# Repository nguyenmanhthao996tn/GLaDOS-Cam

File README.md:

# GLaDOS-Cam

> Edge AI IoT board for vision-based applications

---

## Overview

GLaDOS-Cam is a custom PCB built around the **STM32U575VIT6** (Cortex-M33, 160 MHz) targeting battery-powered, field-deployed TinyML inference. No NPU. No cloud. Runs INT8 inference locally at 1–2 fps which is all that's needed.

---

## Hardware

| # | Component | Manufacturer | Part No. | JLCPCB |
|---|---|---|---|---|
| 1 | MCU | STMicroelectronics | STM32U575**VIT6** | C5270999 |
| 2 | PSRAM | ISSI | IS66WVH8M8BLL-100B1LI | C1349096 |
| 3 | LDO (3.3 V aux) | STMicroelectronics | STLQ020C33R | C2970558 |
| 4 | Camera connector | Hirose | FH12-24S-0.5SH(55) | C202112 |
| 5 | Camera AVDD LDO (2.8 V) | YONGYUTAI | XC6206-2.8V | C2892669 |
| 6 | Camera DVDD LDO (1.2 V) | YONGYUTAI | XC6206-1.2V | C49446790 |
| 7 | Crystal 16 MHz | YXC | X322516MLB4SI | C13738 |
| 8 | Crystal 32.768 kHz | Seiko Epson | Q13FC13500004 | C32346 |
| 9 | Reset button | XKB Connection | TS-1187A-B-A-B | C318884 |
| 10 | MicroSD slot | SHOU HAN | TF-CARD H1.8 | C7529389 |

## Toolchain

| Tool | Purpose |
|---|---|
| KiCad 9 | Schematic + PCB layout |

---

## Repo Structure

```
GLaDOS-Cam/
├── docs/                          # Datasheets, BOM references
│   ├── Component_List.xlsx
│   ├── ESP32_CAM_V1.6.pdf
│   └── NUCLEO-U575ZI-Q/
└── pcb/
    └── GLaDOS-Cam/
        ├── GLaDOS-Cam.kicad_pro   # Project root
        ├── GLaDOS-Cam.kicad_sch   # Top-level schematic
        ├── GLaDOS-Cam.kicad_pcb   # PCB layout
        ├── cam_conn.kicad_sch     # Camera connector sub-sheet
        ├── io_headers.kicad_sch
        ├── mcu.kicad_sch
        ├── microsd.kicad_sch
        ├── power.kicad_sch
        ├── psram.kicad_sch
        └── glados-cam-lib/        # Project-local KiCad library
            ├── glados-cam-lib.pretty/   # Footprints
            │   └── 3d_models/           # STEP files
            └── symbols/
```

---

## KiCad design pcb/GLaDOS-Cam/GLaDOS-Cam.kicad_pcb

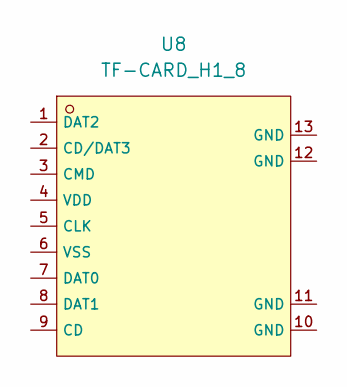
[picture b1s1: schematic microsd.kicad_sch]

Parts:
U8: TF-CARD_H1_8; TF-SMD_TF-CARD-H1.8; LCSC C7529389

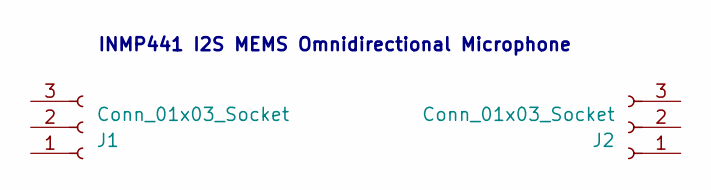
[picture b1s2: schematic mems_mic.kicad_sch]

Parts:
J1, J2: Conn_01x03_Socket; PinSocket_1x03_P2.54mm_Vertical

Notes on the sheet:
INMP441 I2S MEMS Omnidirectional Microphone

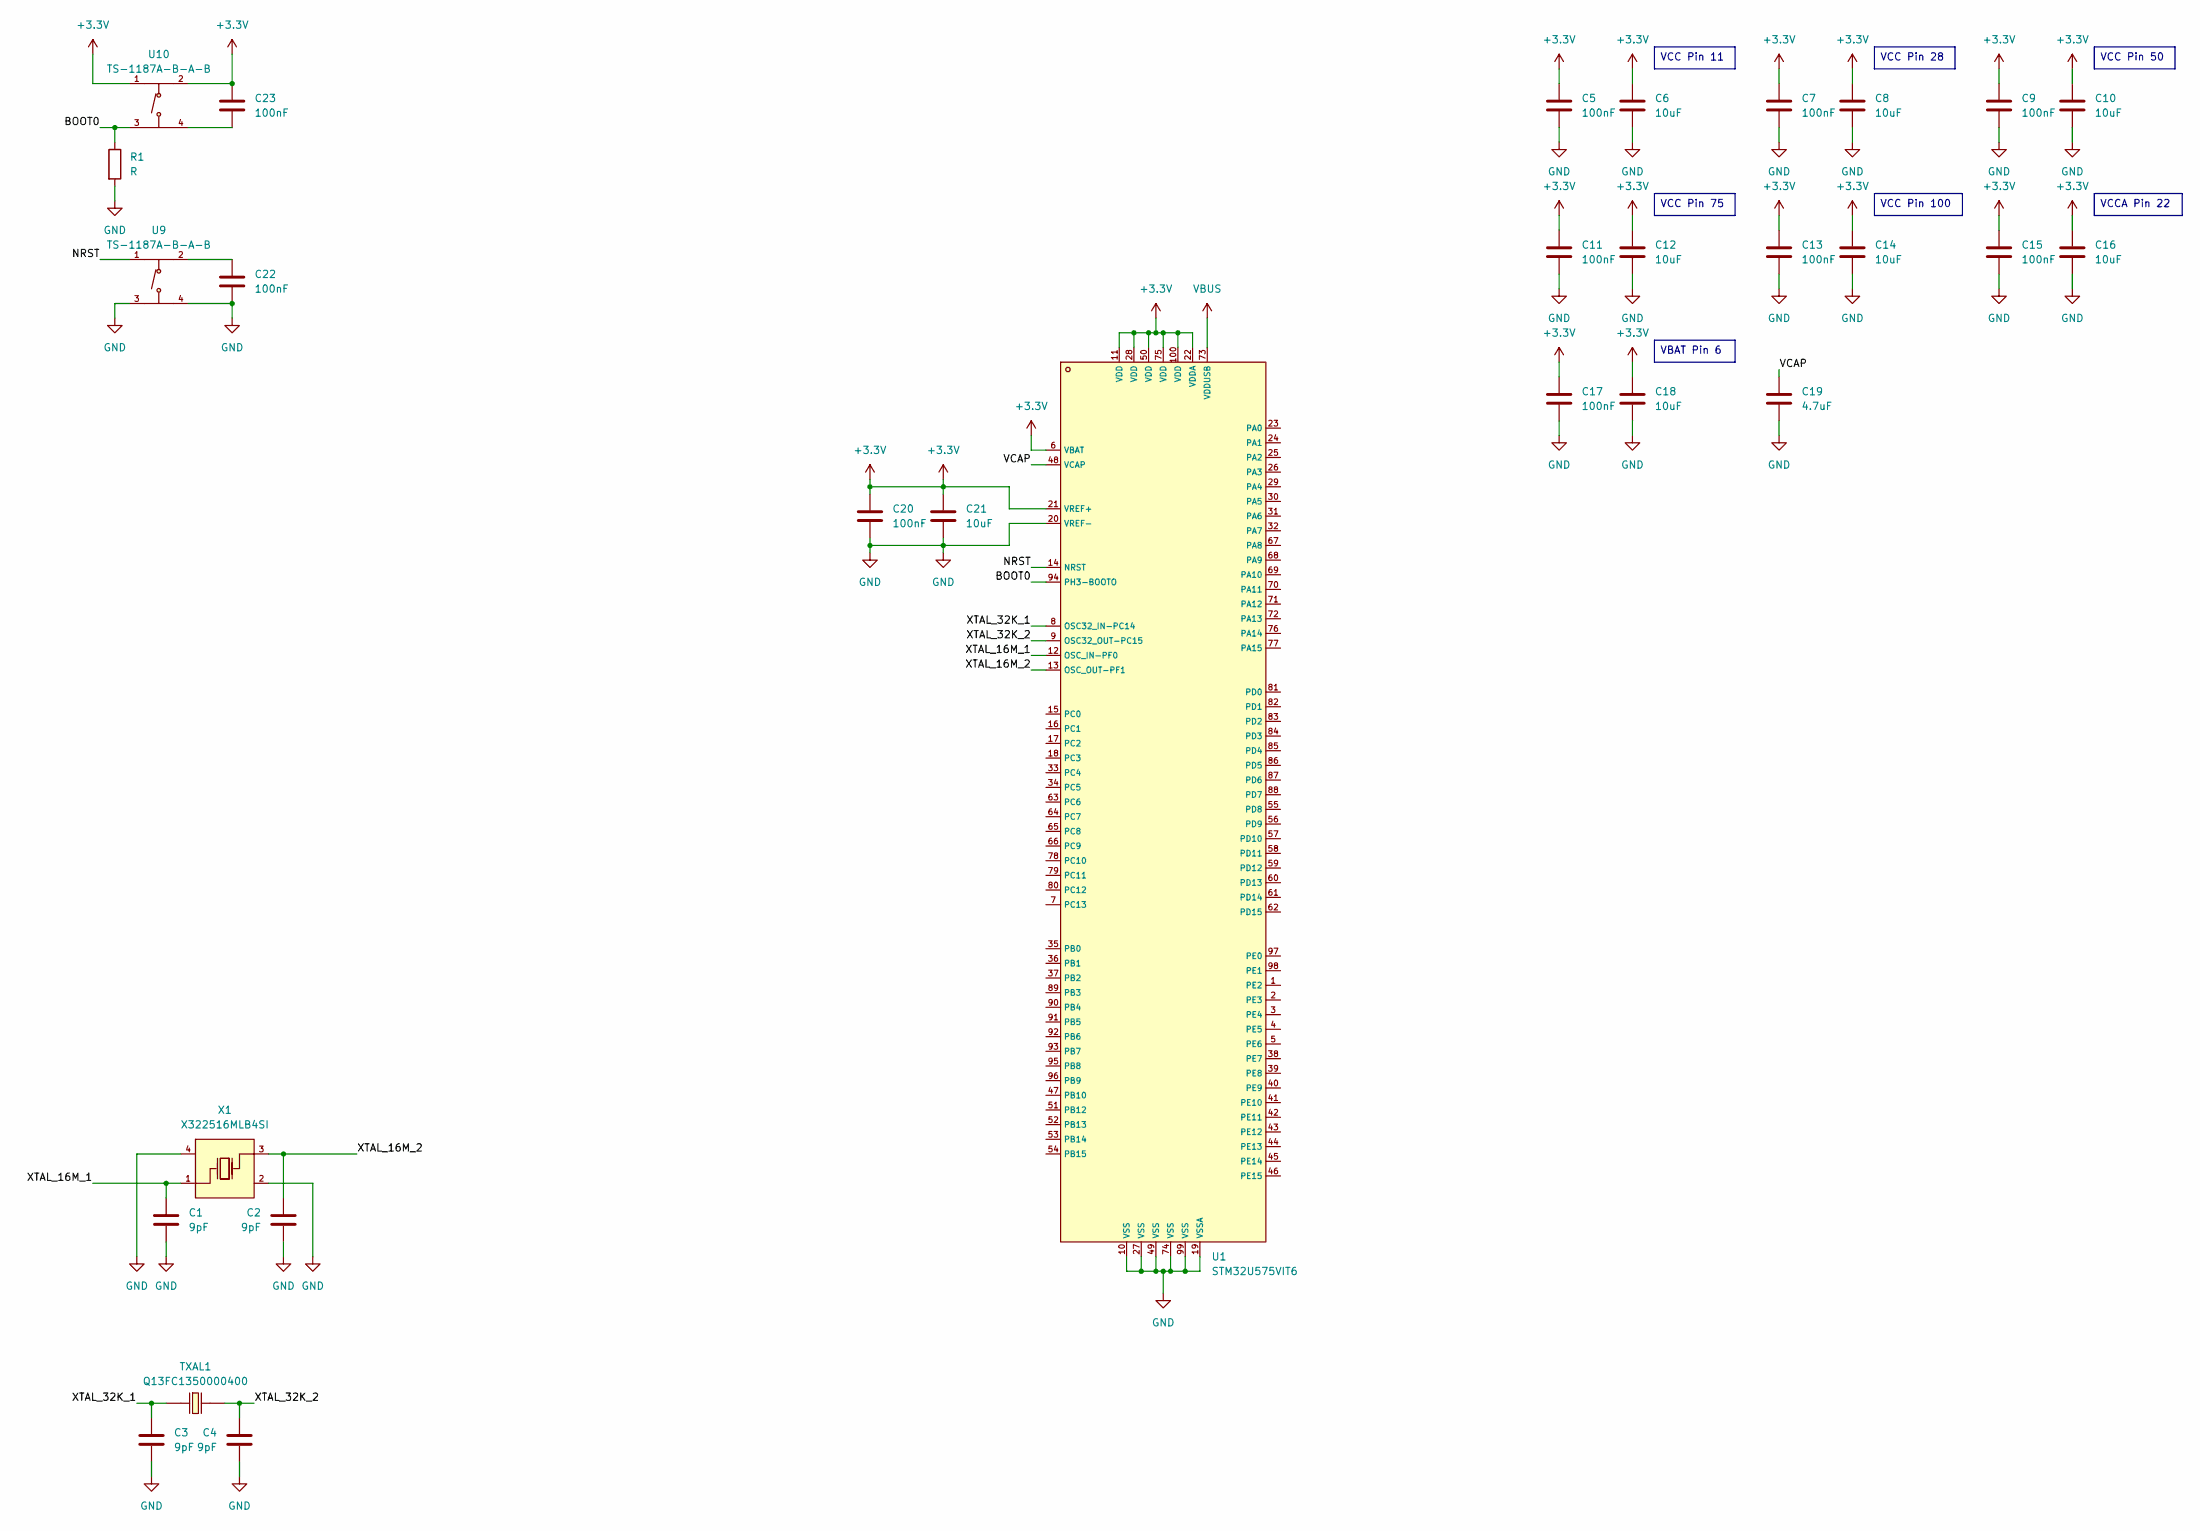
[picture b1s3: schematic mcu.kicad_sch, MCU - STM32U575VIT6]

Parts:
C1, C2, C3, C4: 9pF; C_0603_1608Metric_Pad1.08x0.95mm_HandSolder
C5, C7, C9, C11, C13, C15, C17, C20, C22, C23: 100nF; C_0603_1608Metric_Pad1.08x0.95mm_HandSolder
C6, C8, C10, C12, C14, C16, C18, C21: 10uF; C_0603_1608Metric_Pad1.08x0.95mm_HandSolder
C19: 4.7uF; C_0603_1608Metric_Pad1.08x0.95mm_HandSolder
R1: R; R_0603_1608Metric_Pad0.98x0.95mm_HandSolder
TXAL1: Q13FC1350000400; FC-135R_L3.2-W1.5; LCSC C32346
U1: STM32U575VIT6; LQFP-100_L14.0-W14.0-P0.50-LS16.0-BL; LCSC C5270999
U9, U10: TS-1187A-B-A-B; SW-SMD_4P-L5.1-W5.1-P3.70-LS6.5-TL_H1.5; LCSC C318884
X1: X322516MLB4SI; CRYSTAL-SMD_4P-L3.2-W2.5-BL; LCSC C13738

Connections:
+3.3V: C5.1, C6.1, C7.1, C8.1, C9.1, C10.1, C11.1, C12.1, C13.1, C14.1, C15.1, C16.1, C17.1, C18.1, C20.1, C21.1, C23.1, U1.6 (VBAT), U1.11 (VDD), U1.21 (VREF+), U1.22 (VDDA), U1.28 (VDD), U1.50 (VDD), U1.75 (VDD), U1.100 (VDD), U10.1 (A), U10.2 (B)
/MCU/BOOT0: R1.1, U1.94 (PH3-BOOTO), U10.3 (C)
/MCU/NRST: U1.14 (NRST), U9.1 (A)
/MCU/VCAP: C19.1, U1.48 (VCAP)
/MCU/XTAL_16M_1: C1.1, U1.12 (OSC_IN-PF0), X1.1 (OSC1)
/MCU/XTAL_16M_2: C2.1, U1.13 (OSC_OUT-PF1), X1.3 (OSC2)
/MCU/XTAL_32K_1: C3.1, TXAL1.1, U1.8 (OSC32_IN-PC14)
/MCU/XTAL_32K_2: C4.1, TXAL1.2, U1.9 (OSC32_OUT-PC15)
GND: C1.2, C2.2, C3.2, C4.2, C5.2, C6.2, C7.2, C8.2, C9.2, C10.2, C11.2, C12.2, C13.2, C14.2, C15.2, C16.2, C17.2, C18.2, C19.2, C20.2, C21.2, C22.2, R1.2, U1.10 (VSS), U1.19 (VSSA), U1.20 (VREF-), U1.27 (VSS), U1.49 (VSS), U1.74 (VSS), U1.99 (VSS), U9.3 (C), U9.4 (D), X1.2 (GND), X1.4 (GND)
unnamed: C22.1, U9.2 (B)
unnamed: C23.2, U10.4 (D)
VBUS: U1.73 (VDDUSB)

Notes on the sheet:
VCC Pin 11
VCC Pin 50
VCCA Pin 22
VCC Pin 100
VCC Pin 75
VCC Pin 28
VBAT Pin 6

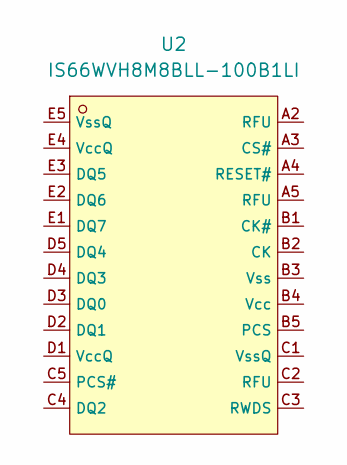
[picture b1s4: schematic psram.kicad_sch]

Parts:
U2: IS66WVH8M8BLL-100B1LI; TFBGA-24_L8.0-W6.0-P1.00-TL_ISSI_ISS66WVH16M8; LCSC C1349096

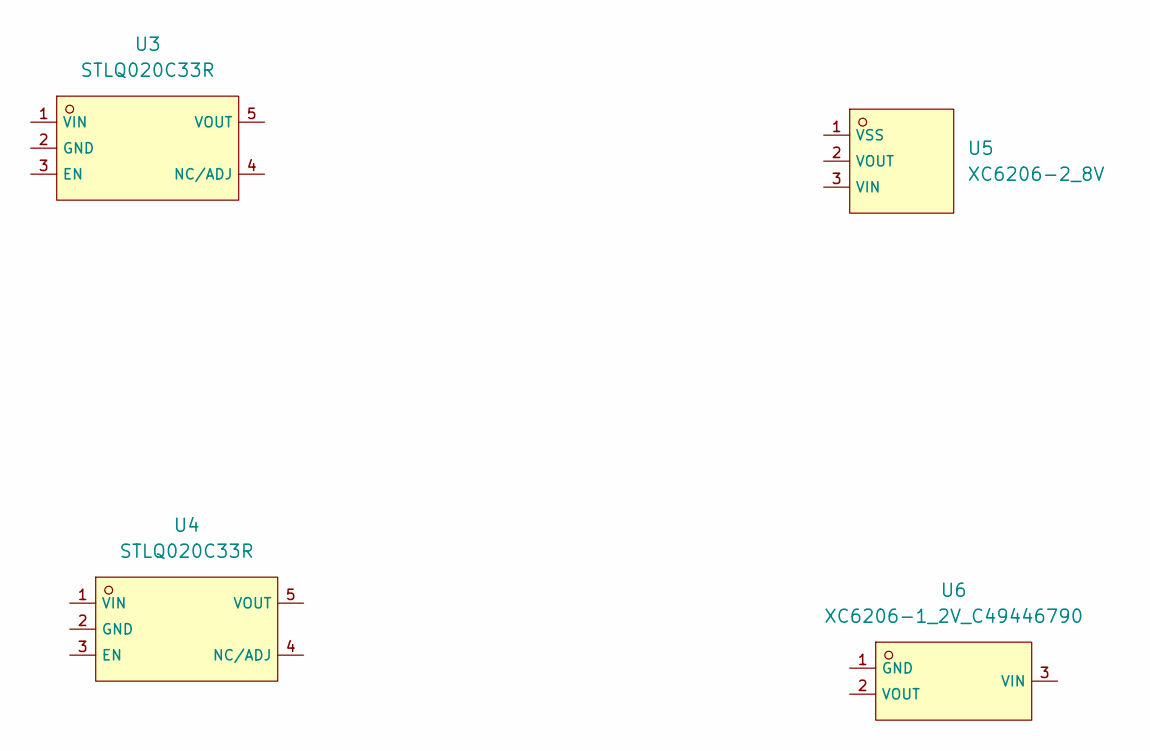
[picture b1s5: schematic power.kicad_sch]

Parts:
U3, U4: STLQ020C33R; TSSOP-5_L2.0-W1.3-P0.65-LS2.1-BL; LCSC C2970558
U5: XC6206-2_8V; SOT-23-3_L2.9-W1.6-P1.90-LS2.8-BR; LCSC C2892669
U6: XC6206-1_2V_C49446790; SOT-23-3_L3.0-W1.6-P1.90-LS2.8-BR; LCSC C49446790

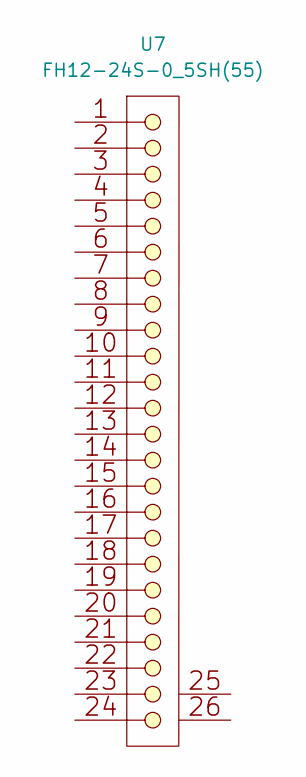
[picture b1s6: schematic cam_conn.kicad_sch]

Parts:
U7: FH12-24S-0_5SH(55); FPC-SMD_FH12-24S-0.5SH-55; LCSC C202112

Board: 2 copper layers, 38 parts (0 on the bottom side), 11 nets, no tracks yet.

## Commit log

2026-05-20 Expand README with hardware and toolchain details
    Added detailed information about hardware components, toolchain, and repository structure.
2026-05-20 Push local devs
2026-05-20 chore: untrack KiCad backups folder
